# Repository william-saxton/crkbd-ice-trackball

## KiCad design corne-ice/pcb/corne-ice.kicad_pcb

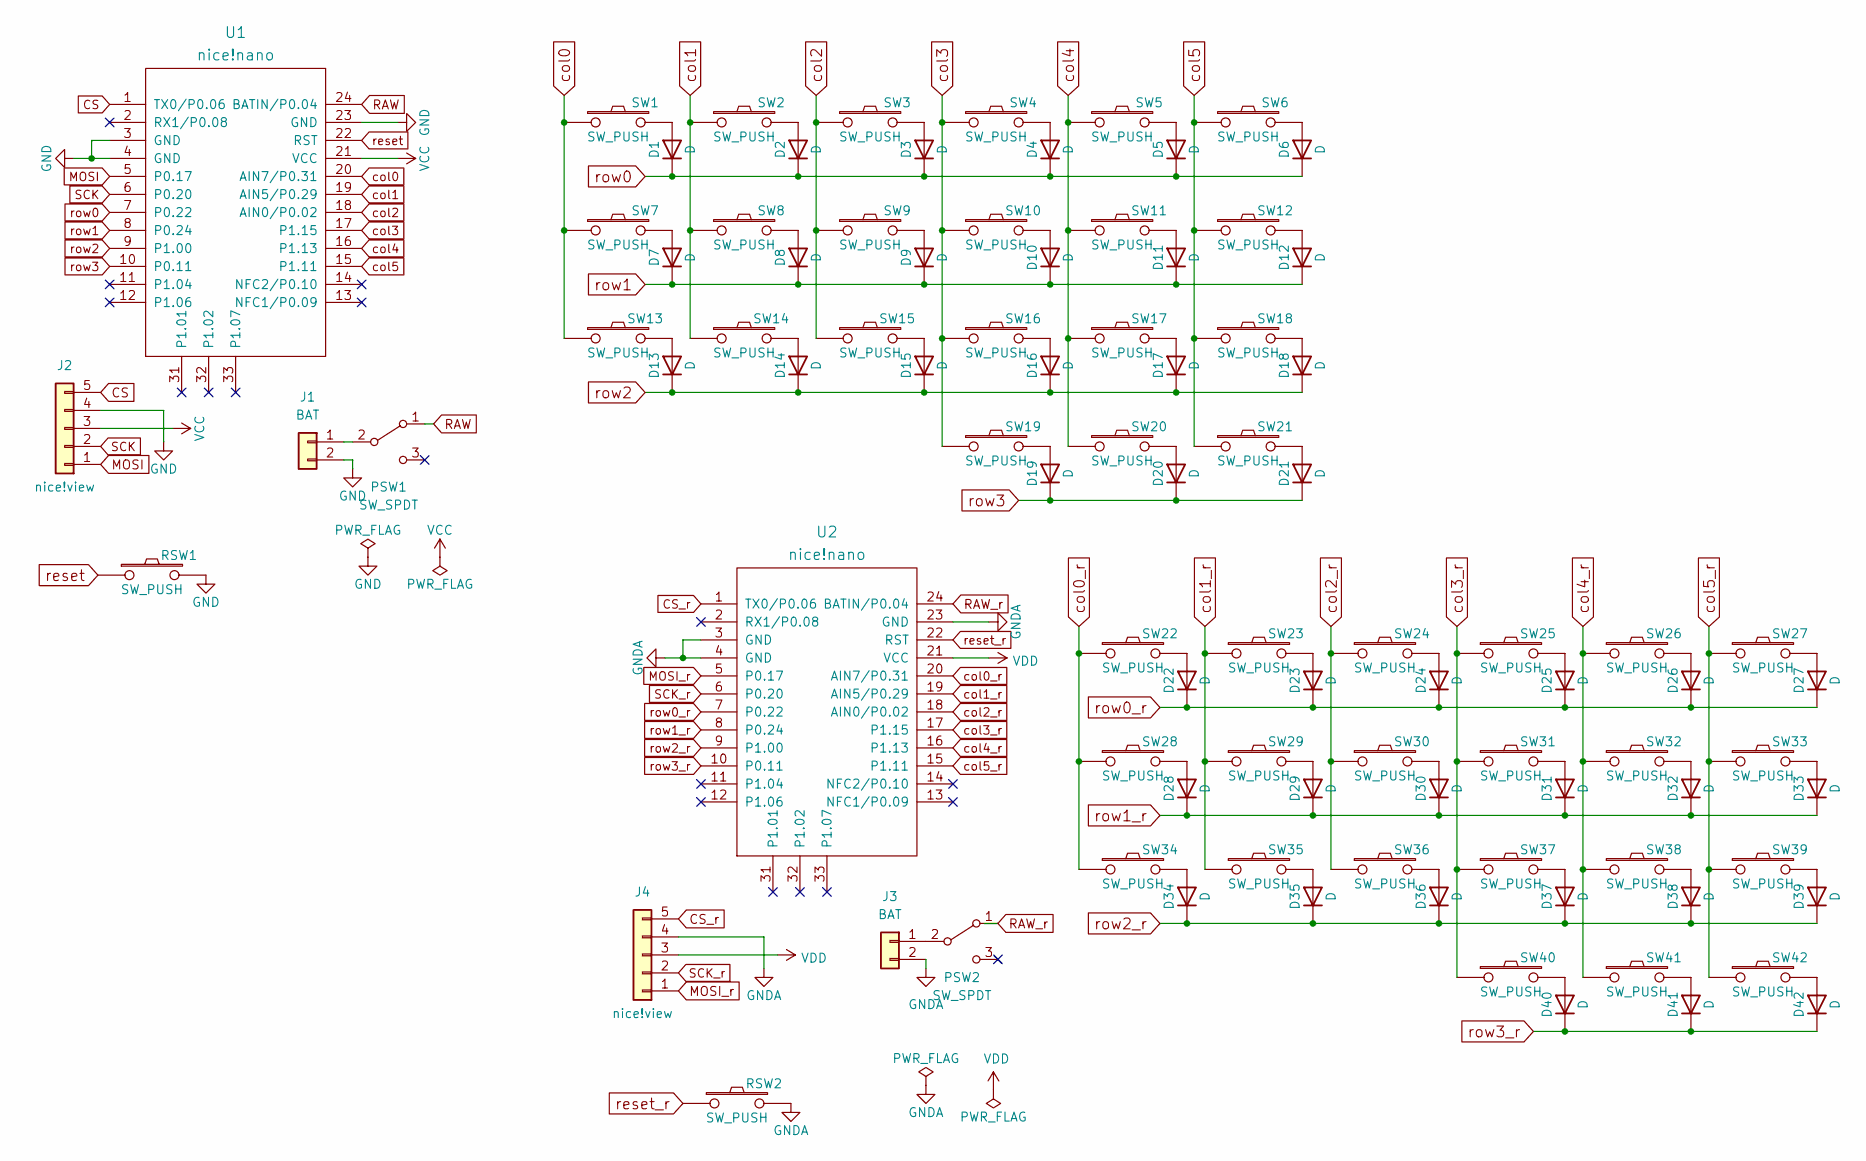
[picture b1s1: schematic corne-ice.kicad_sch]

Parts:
D1, D2, D3, D4, D5, D6, D7, D8, D9, D10, D11, D12, D13, D14, D15, D16, D17, D18, D19, D20, D21, D22, D23, D24, D25, D26, D27, D28, D29, D30, D31, D32, D33, D34, D35, D36, D37, D38, D39, D40, D41, D42: D; D3_SMD_v2
J1, J3: BAT; JST_PH_S2B-PH-SM4-TB_1x02-1MP_P2.00mm_Horizontal
J2, J4: nice!view; PinHeader_1x05_P2.54mm_Vertical
PSW1, PSW2: SW_SPDT; switch_SSSS811101
RSW1, RSW2: SW_PUSH; alps_sksn
SW1, SW2, SW3, SW4, SW5, SW6, SW7, SW8, SW9, SW10, SW11, SW12, SW13, SW14, SW15, SW16, SW17, SW18, SW19, SW20, SW22, SW23, SW24, SW25, SW26, SW27, SW28, SW29, SW30, SW31, SW32, SW33, SW34, SW35, SW36, SW37, SW38, SW39, SW40, SW41: SW_PUSH; CherryMX_Hotswap
SW21, SW42: SW_PUSH; CherryMX_Hotswap_1.5u
U1, U2: nice!nano; ProMicro_v3

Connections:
CS: J2.5, U1.1 (TX0/P0.06)
CS_r: J4.5, U2.1 (TX0/P0.06)
GND: J1.2, J2.4, RSW1.2, U1.3 (GND), U1.4 (GND), U1.23 (GND); also elsewhere on the board
GNDA: J3.2, J4.4, RSW2.2, U2.3 (GND), U2.4 (GND), U2.23 (GND); also elsewhere on the board
MOSI: J2.1, U1.5 (P0.17)
MOSI_r: J4.1, U2.5 (P0.17)
unnamed: D1.2 (A), SW1.2
unnamed: D2.2 (A), SW2.2
unnamed: D3.2 (A), SW3.2
unnamed: D4.2 (A), SW4.2
unnamed: D5.2 (A), SW5.2
unnamed: D6.2 (A), SW6.2
unnamed: D7.2 (A), SW7.2
unnamed: D8.2 (A), SW8.2
unnamed: D9.2 (A), SW9.2
unnamed: D10.2 (A), SW10.2
unnamed: D11.2 (A), SW11.2
unnamed: D12.2 (A), SW12.2
unnamed: D13.2 (A), SW13.2
unnamed: D14.2 (A), SW14.2
unnamed: D15.2 (A), SW15.2
unnamed: D16.2 (A), SW16.2
unnamed: D17.2 (A), SW17.2
unnamed: D18.2 (A), SW18.2
unnamed: D19.2 (A), SW19.2
unnamed: D20.2 (A), SW20.2
unnamed: D21.2 (A), SW21.2
unnamed: D22.2 (A), SW22.2
unnamed: D23.2 (A), SW23.2
unnamed: D24.2 (A), SW24.2
unnamed: D25.2 (A), SW25.2
unnamed: D26.2 (A), SW26.2
unnamed: D27.2 (A), SW27.2
unnamed: D28.2 (A), SW28.2
unnamed: D29.2 (A), SW29.2
unnamed: D30.2 (A), SW30.2
unnamed: D31.2 (A), SW31.2
unnamed: D32.2 (A), SW32.2
unnamed: D33.2 (A), SW33.2
unnamed: D34.2 (A), SW34.2
unnamed: D35.2 (A), SW35.2
unnamed: D36.2 (A), SW36.2
unnamed: D37.2 (A), SW37.2
unnamed: D38.2 (A), SW38.2
unnamed: D39.2 (A), SW39.2
unnamed: D40.2 (A), SW40.2
unnamed: D41.2 (A), SW41.2
unnamed: D42.2 (A), SW42.2
unnamed: J1.1, PSW1.2 (B)
unnamed: J3.1, PSW2.2 (B)
RAW: PSW1.1 (A), U1.24 (BATIN/P0.04)
RAW_r: PSW2.1 (A), U2.24 (BATIN/P0.04)
SCK: J2.2, U1.6 (P0.20)
SCK_r: J4.2, U2.6 (P0.20)
VCC: J2.3, U1.21 (VCC)
VDD: J4.3, U2.21 (VCC)
col0: SW1.1, SW7.1, SW13.1, U1.20 (AIN7/P0.31)
col0_r: SW22.1, SW28.1, SW34.1, U2.20 (AIN7/P0.31)
col1: SW2.1, SW8.1, SW14.1, U1.19 (AIN5/P0.29)
col1_r: SW23.1, SW29.1, SW35.1, U2.19 (AIN5/P0.29)
col2: SW3.1, SW9.1, SW15.1, U1.18 (AIN0/P0.02)
col2_r: SW24.1, SW30.1, SW36.1, U2.18 (AIN0/P0.02)
col3: SW4.1, SW10.1, SW16.1, SW19.1, U1.17 (P1.15)
col3_r: SW25.1, SW31.1, SW37.1, SW40.1, U2.17 (P1.15)
col4: SW5.1, SW11.1, SW17.1, SW20.1, U1.16 (P1.13)
col4_r: SW26.1, SW32.1, SW38.1, SW41.1, U2.16 (P1.13)
col5: SW6.1, SW12.1, SW18.1, SW21.1, U1.15 (P1.11)
col5_r: SW27.1, SW33.1, SW39.1, SW42.1, U2.15 (P1.11)
reset: RSW1.1, U1.22 (RST); also elsewhere on the board
reset_r: RSW2.1, U2.22 (RST); also elsewhere on the board
row0: D1.1 (K), D2.1 (K), D3.1 (K), D4.1 (K), D5.1 (K), D6.1 (K), U1.7 (P0.22)
row0_r: D22.1 (K), D23.1 (K), D24.1 (K), D25.1 (K), D26.1 (K), D27.1 (K), U2.7 (P0.22)
row1: D7.1 (K), D8.1 (K), D9.1 (K), D10.1 (K), D11.1 (K), D12.1 (K), U1.8 (P0.24)
row1_r: D28.1 (K), D29.1 (K), D30.1 (K), D31.1 (K), D32.1 (K), D33.1 (K), U2.8 (P0.24)
row2: D13.1 (K), D14.1 (K), D15.1 (K), D16.1 (K), D17.1 (K), D18.1 (K), U1.9 (P1.00)
row2_r: D34.1 (K), D35.1 (K), D36.1 (K), D37.1 (K), D38.1 (K), D39.1 (K), U2.9 (P1.00)
row3: D19.1 (K), D20.1 (K), D21.1 (K), U1.10 (P0.11)
row3_r: D40.1 (K), D41.1 (K), D42.1 (K), U2.10 (P0.11)

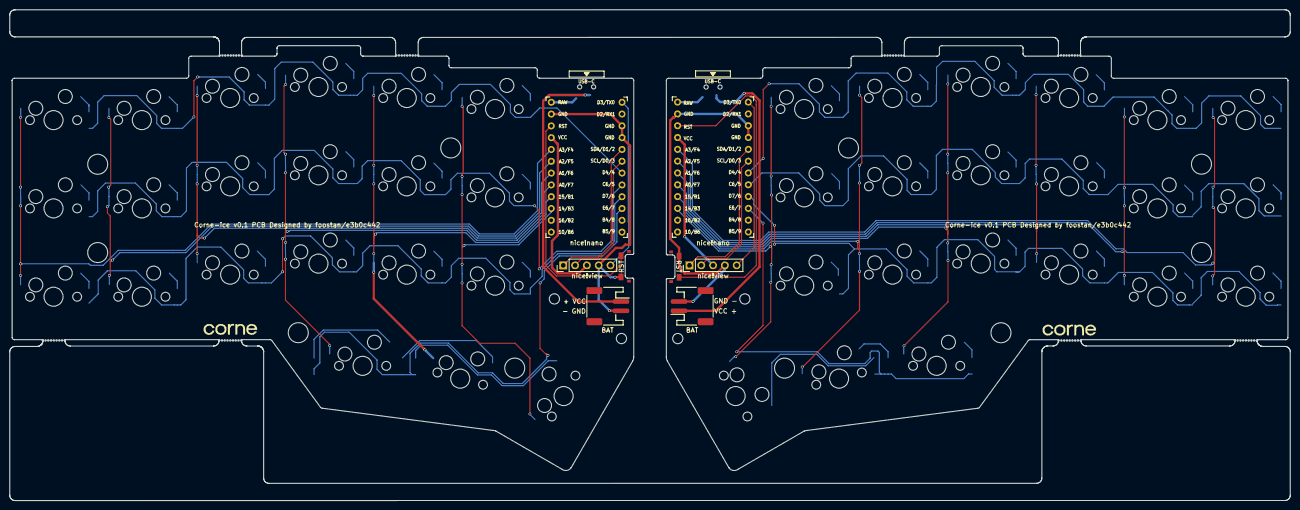
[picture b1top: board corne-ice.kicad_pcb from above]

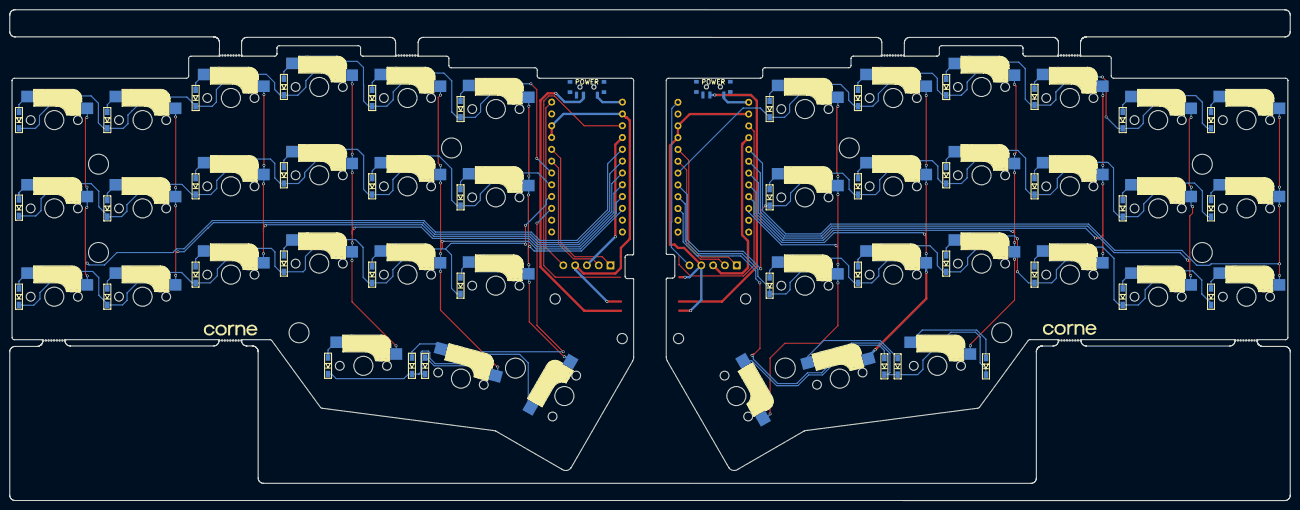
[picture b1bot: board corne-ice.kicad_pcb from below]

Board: 2 copper layers, 275.5 x 105.6 mm, 108 parts (47 on the bottom side), 78 nets.

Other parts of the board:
RST: SW_PUSH; alps_sksn
RST#2: SW_PUSH; alps_sksn
Ref**: Val**; M2_HOLE_v2
Ref**#2, Ref**#3, Ref**#4, Ref**#5, Ref**#6, Ref**#7, Ref**#8, Ref**#9, Ref**#10, Ref**#11, Ref**#12, Ref**#13, Ref**#14: Val**; M2_HOLE_v2

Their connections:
GND: RST.2; also elsewhere on the board
GNDA: RST#2.2; also elsewhere on the board
reset: RST.1; also elsewhere on the board
reset_r: RST#2.1; also elsewhere on the board

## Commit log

2022-10-09 copy corne-cherry; remove leds; clean up nets
2022-10-09 mx -> choc hotswap sockets
2022-10-09 add nice!nano, replace Pro Micro footprints with nice!nano
2022-10-10 complete battery jumper and power switch, clean up nets again
2022-10-10 finish switches and nice!view
2022-10-10 tweak footprints
2022-10-11 revert reset switches
2022-10-16 complete layout and traces
2022-10-19 new svgs
2022-10-21 add front and back
2022-10-21 add pcb
2022-11-18 better labeling
2022-12-17 update build guide
2022-12-17 start corne-ice; remove leds
2022-12-17 remove trrs
2022-12-17 cleanup tracks
2022-12-17 update oled footprint and reroute
2022-12-17 fix battery label on cho-corne-ice
2022-12-17 forgot to save schematic
2022-12-17 reset switch cutout
2022-12-17 place remaining footprints
2022-12-17 fix all routes, pass erc
2022-12-17 clean up, add gerber files
2022-12-17 ACTUALLY add gerbers
2024-08-05 Added light ice trackball inital design.
